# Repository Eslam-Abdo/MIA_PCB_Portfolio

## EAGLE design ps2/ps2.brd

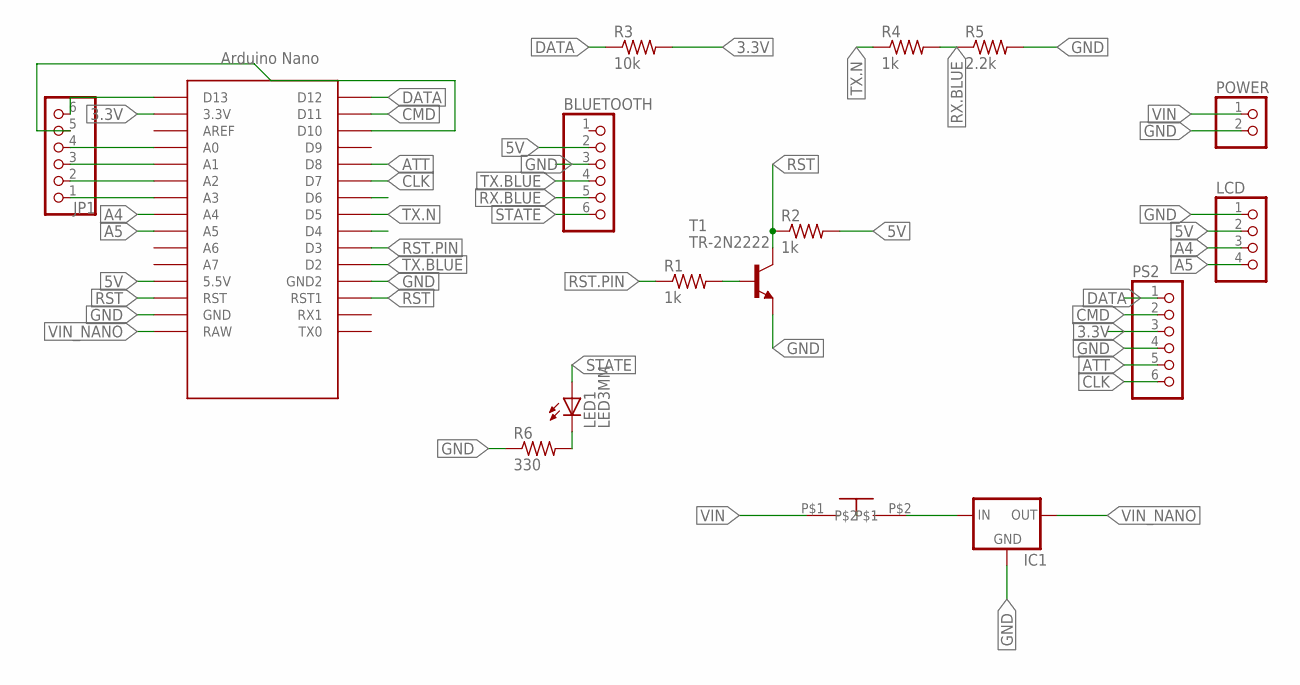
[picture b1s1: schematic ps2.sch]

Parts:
BLUETOOTH: PINHD-1X6; 1X06
IC1: 78XXS
JP1: PINHD-1X6; 1X06
LCD: PINHD-1X4; 1X04
LED1: LED3MM
POWER: PINHD-1X2; 1X02
PS2: PINHD-1X6; 1X06
R1, R2, R4: 1k; 0204/5
R3: 10k; 0204/5
R5: 2.2k; 0204/5
R6: 330; 0204/5
T1: TR-2N2222; TO18
U$1: ARDUINO_NANO; NANO
U$2: SWITCH_2; ON_OFF

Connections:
3.3V: PS2.3, R3.2, U$1.3.3V
5V: BLUETOOTH.2, LCD.2, R2.2, U$1.5V (5.5V)
A4: LCD.3, U$1.A4
A5: LCD.4, U$1.A5
ATT: PS2.5, U$1.D8
CLK: PS2.6, U$1.D7
CMD: PS2.2, U$1.D11
DATA: PS2.1, R3.1, U$1.D12
GND: BLUETOOTH.3, IC1.GND, LCD.1, POWER.2, PS2.4, R5.2, R6.1, T1.1 (E), U$1.GND, U$1.GND1 (GND2)
unnamed: R1.2, T1.2 (B)
unnamed: JP1.1, U$1.A3
unnamed: LED1.K (C), R6.2
unnamed: JP1.2, U$1.A2
unnamed: JP1.3, U$1.A1
unnamed: JP1.4, U$1.A0
unnamed: JP1.6, U$1.D13
unnamed: JP1.5, U$1.D10
unnamed: IC1.IN, U$2.P$2
RST: R2.1, T1.3 (C), U$1.RST, U$1.RST1
RST.PIN: R1.1, U$1.D3
RX.BLUE: BLUETOOTH.5, R4.2, R5.1
STATE: BLUETOOTH.6, LED1.A
TX.BLUE: BLUETOOTH.4, U$1.D2
TX.N: R4.1, U$1.D5
VIN: POWER.1, U$2.P$1
VIN_NANO: IC1.OUT, U$1.RAW

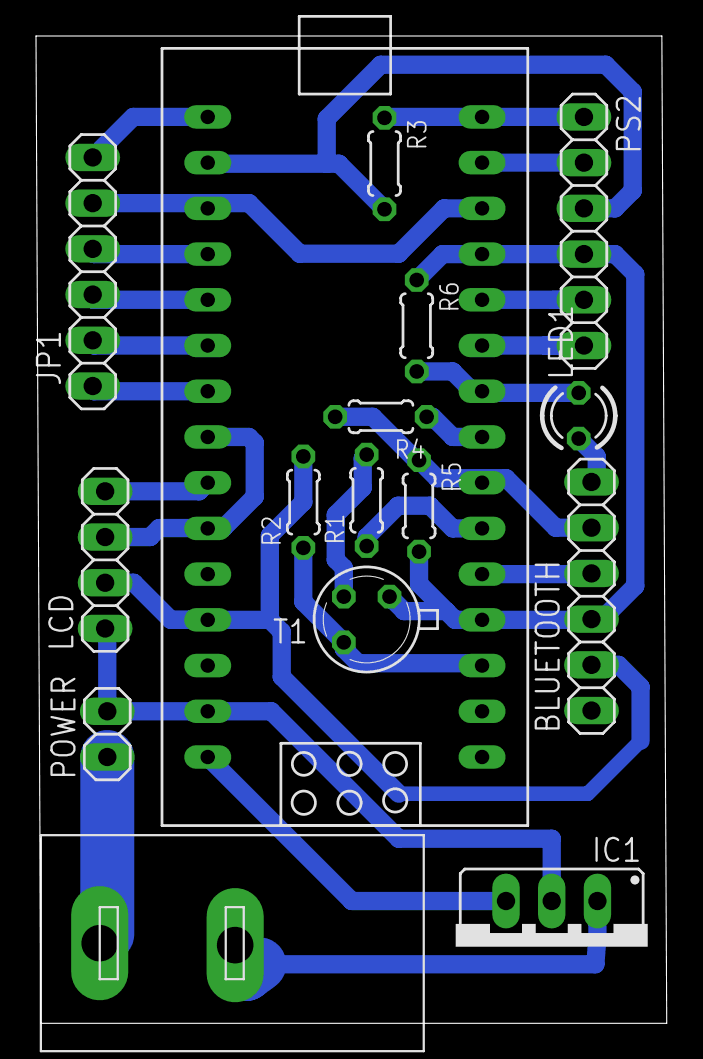
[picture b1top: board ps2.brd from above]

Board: 2 copper layers, 35.0 x 54.9 mm, 16 parts (0 on the bottom side), 26 nets.

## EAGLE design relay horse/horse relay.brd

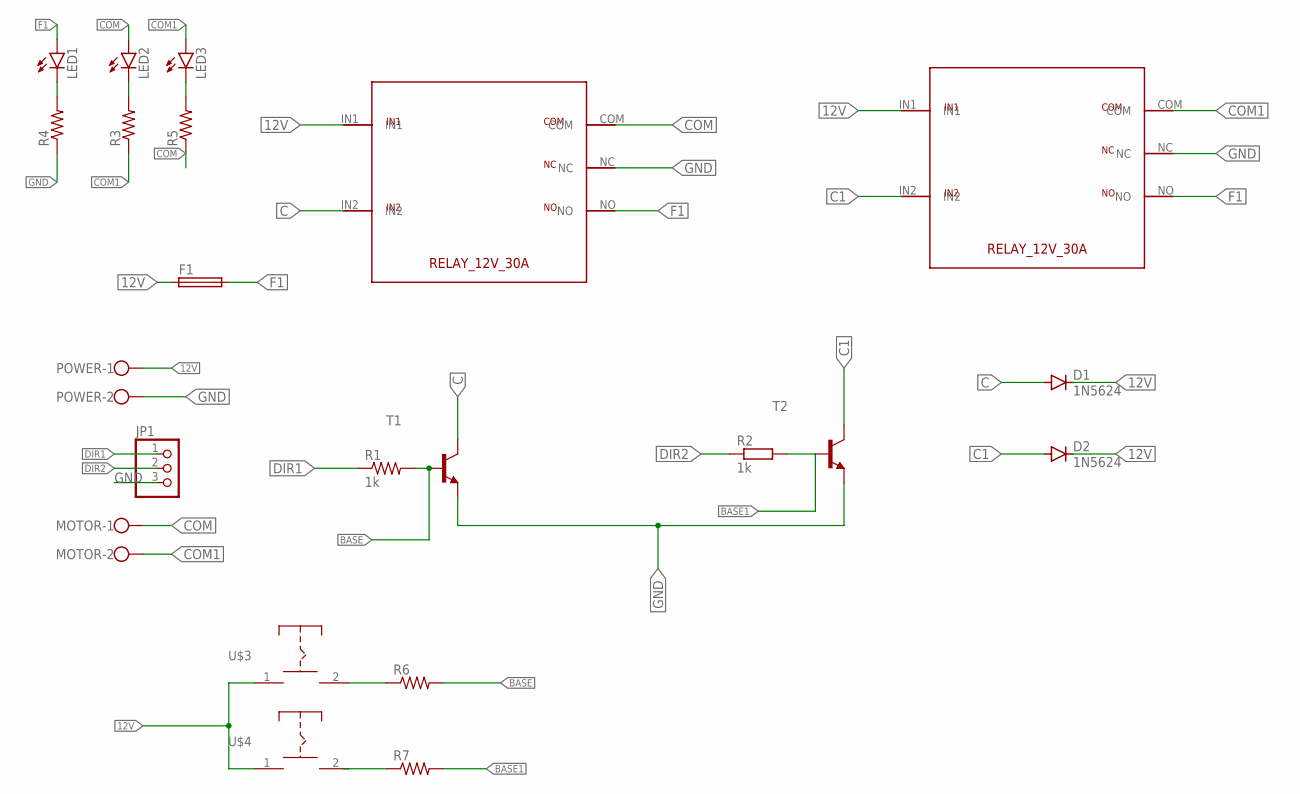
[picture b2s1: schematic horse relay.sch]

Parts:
D1, D2: 1N5624; DO201-15
F1: SH22,5A
JP1: PINHD-1X3; 1X03
LED1: LED5MM
LED2, LED3: LED3MM
MOTOR: W237-113
POWER: W237-113
R1: 1k; 0207/10
R2: 1k; 0204/7
R3, R6: R-US_0207/12; 0207/12
R4, R7: R-US_0204/7; 0204/7
R5: R-US_0207/15; 0207/15
T1, T2: 2N3904-NPN-TO92-EBC; TO92-EBC
U$1, U$2: RELAY_12V_30A
U$3, U$4: PUSHBOTTON

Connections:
12V: D1.C, D2.C, F1.1, POWER.1, U$1.IN1, U$2.IN1, U$3.1, U$4.1
BASE: R1.2, R6.2, T1.B
BASE1: R2.2, R7.2, T2.B
C: D1.A, T1.C, U$1.IN2
C1: D2.A, T2.C, U$2.IN2
COM: LED2.A, MOTOR.1, R5.1, U$1.COM
COM1: LED3.A, MOTOR.2, R3.1, U$2.COM
DIR1: JP1.1, R1.1
DIR2: JP1.2, R2.1
F1: F1.2, LED1.A, U$1.NO, U$2.NO
GND: JP1.3, POWER.2, R4.1, T1.E, T2.E, U$1.NC, U$2.NC
unnamed: LED1.K (C), R4.2
unnamed: LED2.K (C), R3.2
unnamed: LED3.K (C), R5.2
unnamed: R7.1, U$4.2
unnamed: R6.1, U$3.2

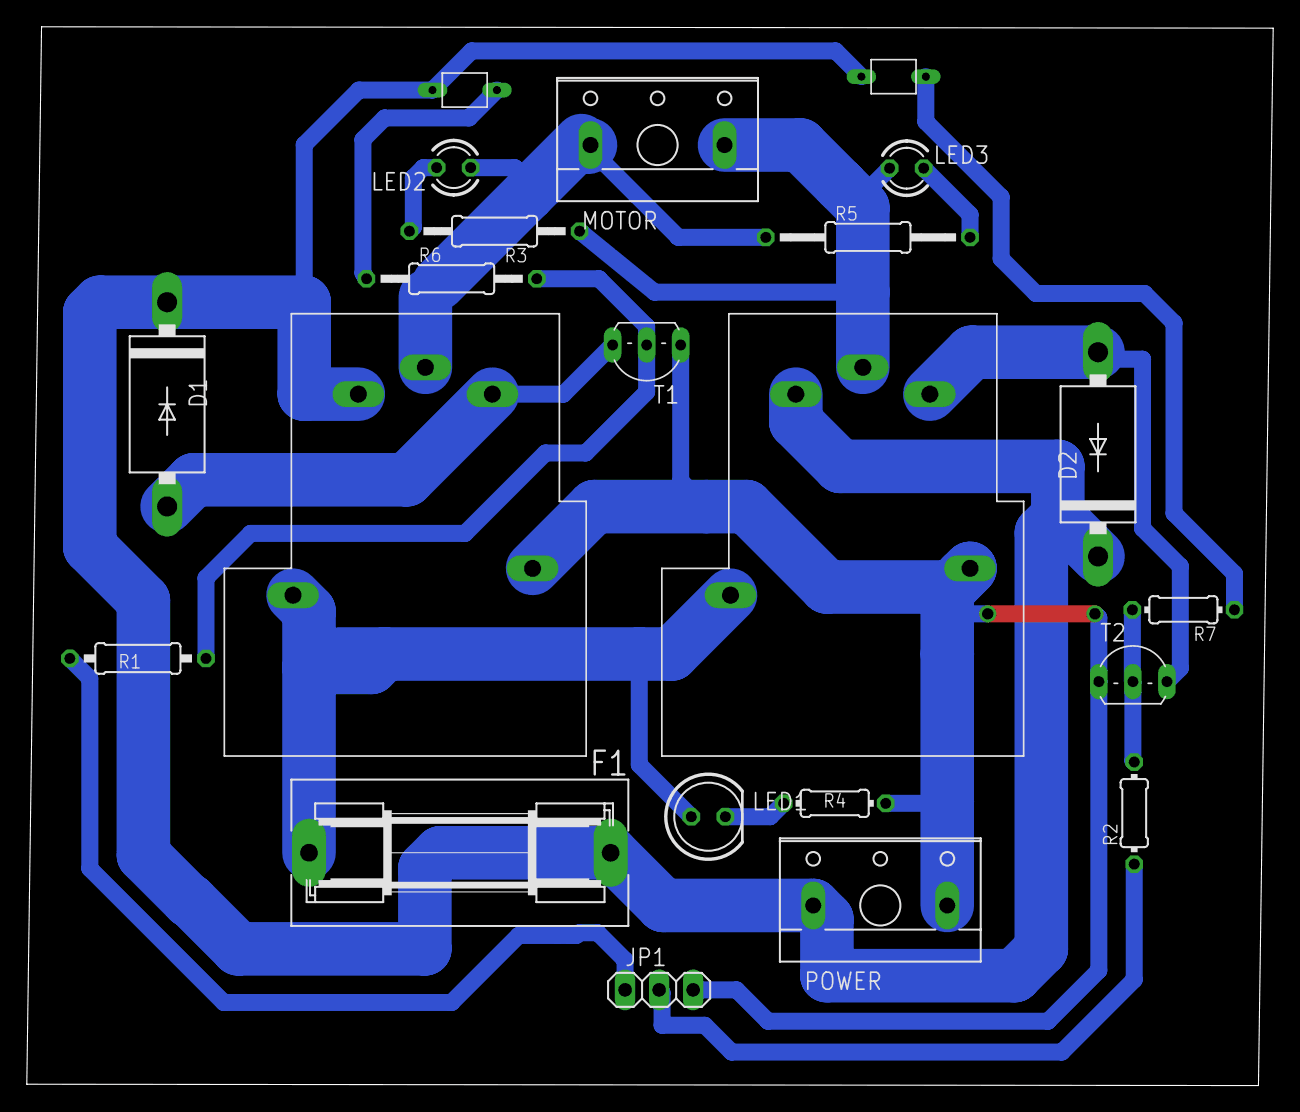
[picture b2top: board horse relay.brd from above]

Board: 2 copper layers, 93.0 x 79.0 mm, 22 parts (0 on the bottom side), 16 nets.

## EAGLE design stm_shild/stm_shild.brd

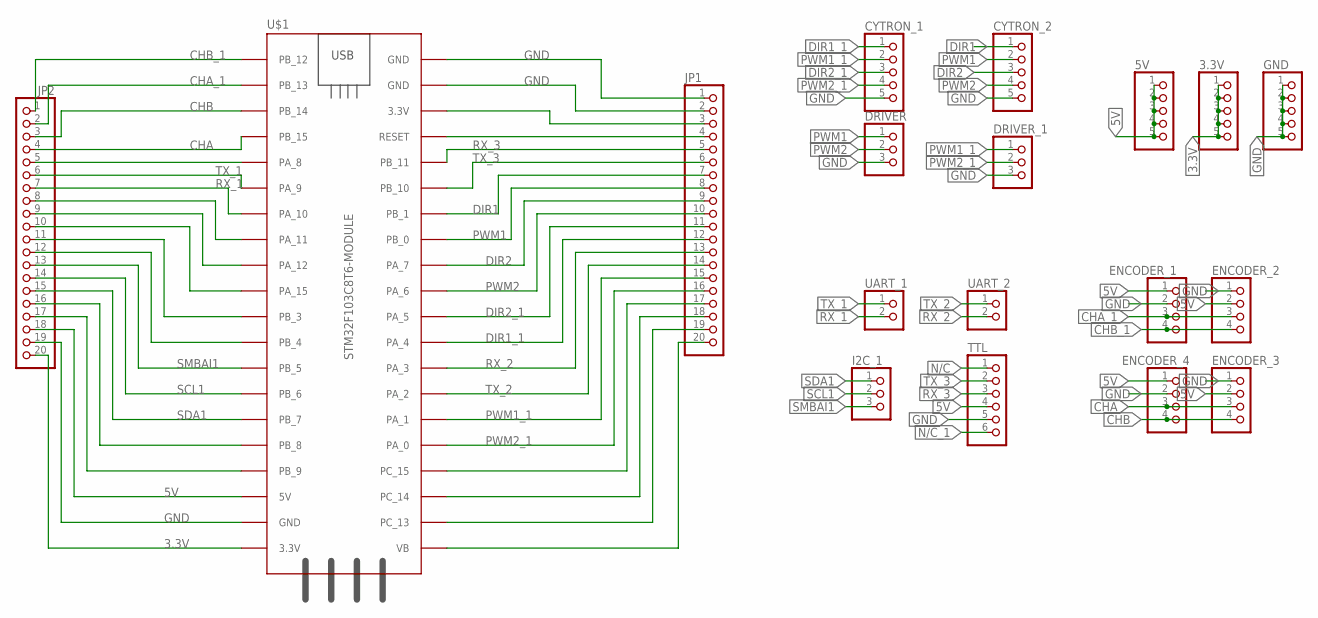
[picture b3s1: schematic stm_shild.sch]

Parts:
3.3V, 5V: PINHD-1X5; 1X05
CYTRON_1, CYTRON_2: PINHD-1X5; 1X05
DRIVER: PINHD-1X3; 1X03
DRIVER_1: PINHD-1X3; 1X03
ENCODER_1, ENCODER_2, ENCODER_3, ENCODER_4: PINHD-1X4; 1X04
GND: PINHD-1X5; 1X05
I2C_1: PINHD-1X3; 1X03
JP1, JP2: PINHD-1X20; 1X20
TTL: PINHD-1X6; 1X06
U$1: STM32F103C8T6-MODULE
UART_1, UART_2: PINHD-1X2; 1X02

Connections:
3.3V: 3.3V.1, 3.3V.2, 3.3V.3, 3.3V.4, 3.3V.5, JP2.20, U$1.3.3V_1 (3.3V)
5V: 5V.1, 5V.2, 5V.3, 5V.4, 5V.5, ENCODER_1.1, ENCODER_2.2, ENCODER_3.2, ENCODER_4.1, JP2.18, TTL.4, U$1.5V
8183: JP2.17, U$1.PB_9
823828: JP2.16, U$1.PB_8
CHA: ENCODER_3.3, ENCODER_4.3, JP2.4, U$1.PB_15
CHA_1: ENCODER_1.3, ENCODER_2.3, JP2.2, U$1.PB_13
CHB: ENCODER_3.4, ENCODER_4.4, JP2.3, U$1.PB_14
CHB_1: ENCODER_1.4, ENCODER_2.4, JP2.1, U$1.PB_12
DIR1: CYTRON_2.1, JP1.7, U$1.PB_1
DIR1_1: CYTRON_1.1, JP1.12, U$1.PA_4
DIR2: CYTRON_2.3, JP1.9, U$1.PA_7
DIR2_1: CYTRON_1.3, JP1.11, U$1.PA_5
GND: CYTRON_1.5, CYTRON_2.5, DRIVER.3, DRIVER_1.3, ENCODER_1.2, ENCODER_2.1, ENCODER_3.1, ENCODER_4.2, GND.1, GND.2, GND.3, GND.4, GND.5, JP1.1, JP1.2, JP2.19, TTL.5, U$1.GND_1 (GND), U$1.GND_2 (GND), U$1.GND_3 (GND)
unnamed: JP1.20, U$1.VB
unnamed: JP1.3, U$1.3.3V_2 (3.3V)
unnamed: JP1.4, U$1.RESET
unnamed: JP1.17, U$1.PC_15
unnamed: JP1.18, U$1.PC_14
unnamed: JP1.19, U$1.PC_13
unnamed: JP2.5, U$1.PA_8
unnamed: JP2.8, U$1.PA_11
unnamed: JP2.9, U$1.PA_12
unnamed: JP2.10, U$1.PA_15
unnamed: JP2.11, U$1.PB_3
unnamed: JP2.12, U$1.PB_4
N/C: TTL.1
N/C_1: TTL.6
PWM1: CYTRON_2.2, DRIVER.1, JP1.8, U$1.PB_0
PWM1_1: CYTRON_1.2, DRIVER_1.1, JP1.15, U$1.PA_1
PWM2: CYTRON_2.4, DRIVER.2, JP1.10, U$1.PA_6
PWM2_1: CYTRON_1.4, DRIVER_1.2, JP1.16, U$1.PA_0
RX_1: JP2.7, U$1.PA_10, UART_1.2
RX_2: JP1.13, U$1.PA_3, UART_2.2
RX_3: JP1.5, TTL.3, U$1.PB_11
SCL1: I2C_1.2, JP2.14, U$1.PB_6
SDA1: I2C_1.1, JP2.15, U$1.PB_7
SMBAI1: I2C_1.3, JP2.13, U$1.PB_5
TX_1: JP2.6, U$1.PA_9, UART_1.1
TX_2: JP1.14, U$1.PA_2, UART_2.1
TX_3: JP1.6, TTL.2, U$1.PB_10

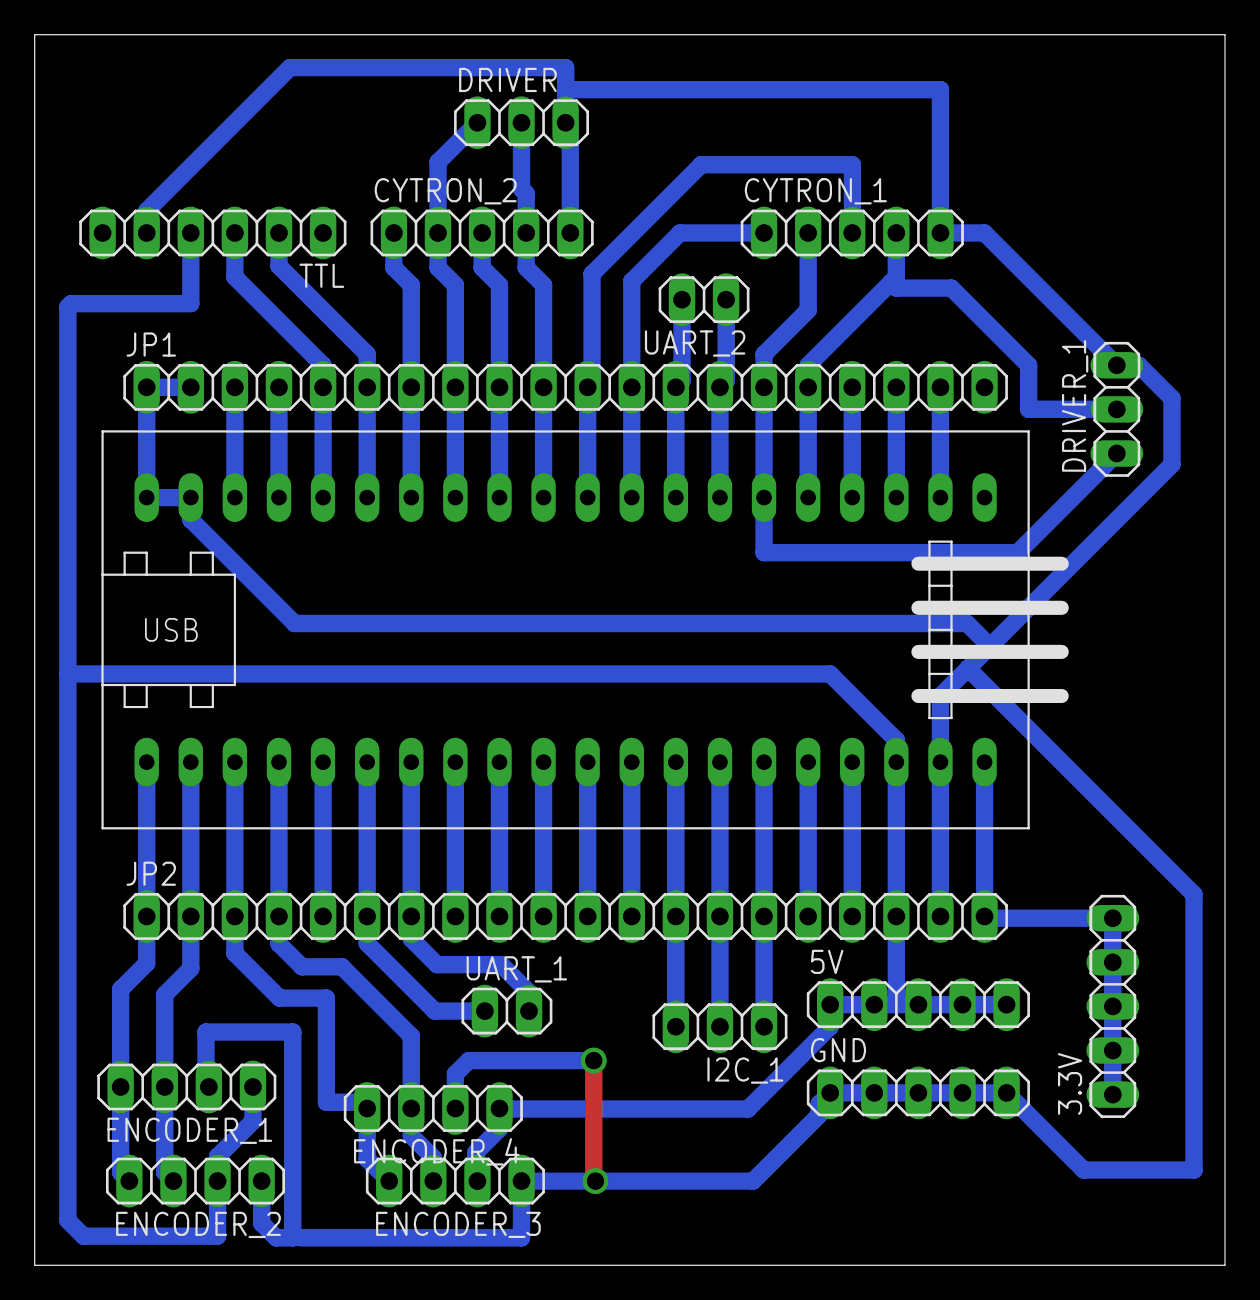
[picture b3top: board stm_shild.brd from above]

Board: 2 copper layers, 68.6 x 70.9 mm, 18 parts (0 on the bottom side), 38 nets.

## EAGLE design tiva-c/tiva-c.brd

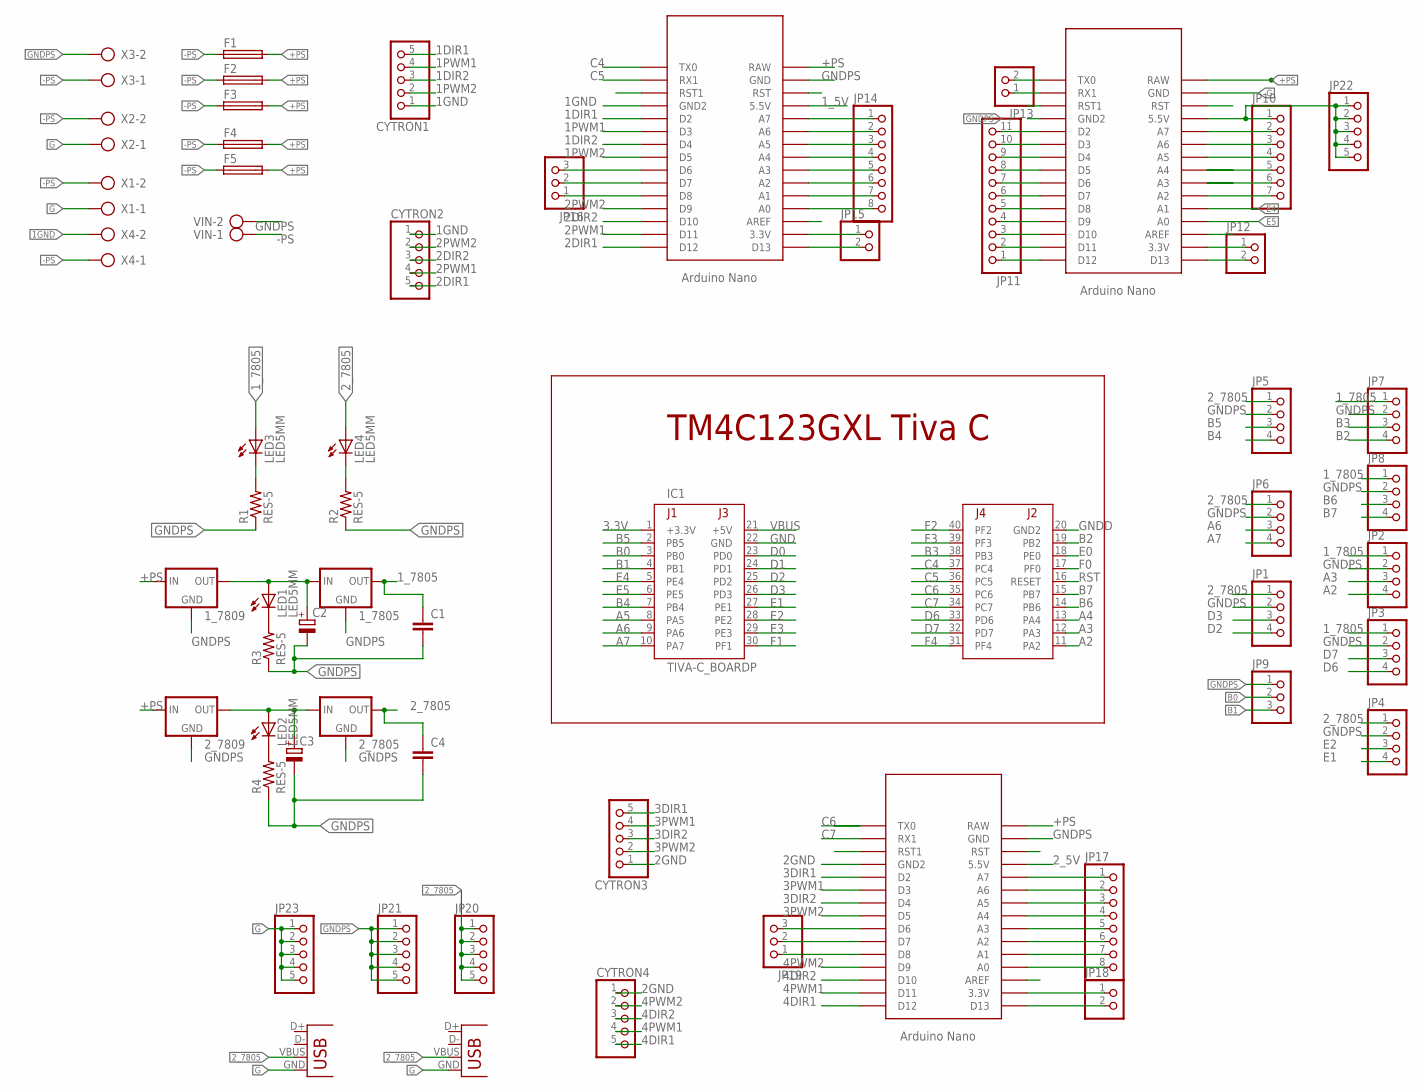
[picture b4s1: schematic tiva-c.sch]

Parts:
1_7805, 1_7809, 2_7805, 2_7809: 78XXS
C1, C4: CAPACITOR; C025-025X050
C2, C3: CAP_POL; E3,5-8
CYTRON1, CYTRON2, CYTRON3, CYTRON4: PINHD-1X5; 1X05
F1, F2, F3, F4, F5: FUSE_HOLDER; SH22,5A
IC1: TIVA-C_BOARDP; TM4C123LAUNCHPAD
JP1, JP2, JP3, JP4, JP5, JP6, JP7, JP8: PINHD-1X4; 1X04
JP9, JP16, JP19: PINHD-1X3; 1X03
JP10: PINHD-1X7; 1X07
JP11: PINHD-1X11; 1X11
JP12, JP13, JP15, JP18: PINHD-1X2; 1X02
JP14, JP17: PINHD-1X8; 1X08
JP20, JP21, JP22, JP23: PINHD-1X5; 1X05
LED1, LED2, LED3, LED4: LED5MM
R1, R2, R3, R4: RES-5; 0204/5
U$1, U$2, U$3: ARDUINO_NANO; NANO
VIN: CON_PTR_2(V_2); AK300/2
X1, X2, X3, X4: CON_PTR_2(V_2); AK300/2
X5, X6: USB-A-H

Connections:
1DIR1: CYTRON1.5, U$3.D2
1DIR2: CYTRON1.3, U$3.D4
1GND: CYTRON1.1, CYTRON2.1, U$3.GND1 (GND2), X4.2
1PWM1: CYTRON1.4, U$3.D3
1PWM2: CYTRON1.2, U$3.D5
1_5V: U$3.5V (5.5V)
1_7805: 1_7805.OUT, C1.1, JP2.1, JP3.1, JP7.1, JP8.1, LED3.A
2DIR1: CYTRON2.5, U$3.D12
2DIR2: CYTRON2.3, U$3.D10
2GND: CYTRON3.1, CYTRON4.1, U$1.GND1 (GND2)
2PWM1: CYTRON2.4, U$3.D11
2PWM2: CYTRON2.2, U$3.D9
2_5V: U$1.5V (5.5V)
2_7805: 2_7805.OUT, C4.1, JP1.1, JP4.1, JP5.1, JP6.1, JP20.1, JP20.2, JP20.3, JP20.4, JP20.5, LED4.A, X5.VBUS, X6.VBUS
3.3V: IC1.1 (+3.3V)
3DIR1: CYTRON3.5, U$1.D2
3DIR2: CYTRON3.3, U$1.D4
3PWM1: CYTRON3.4, U$1.D3
3PWM2: CYTRON3.2, U$1.D5
4DIR1: CYTRON4.5, U$1.D12
4DIR2: CYTRON4.3, U$1.D10
4PWM1: CYTRON4.4, U$1.D11
4PWM2: CYTRON4.2, U$1.D9
+PS: 1_7809.IN, 2_7809.IN, F1.2, F2.2, F3.2, F4.2, F5.2, U$1.RAW, U$2.RAW, U$3.RAW
-PS: F1.1, F2.1, F3.1, F4.1, F5.1, VIN.1, X1.2, X2.2, X3.1, X4.1
A2: IC1.11 (PA2), JP2.4
A3: IC1.12 (PA3), JP2.3
A4: IC1.13 (PA4)
A5: IC1.8 (PA5)
A6: IC1.9 (PA6), JP6.3
A7: IC1.10 (PA7), JP6.4
B0: IC1.3 (PB0), JP9.2
B1: IC1.4 (PB1), JP9.3
B2: IC1.19 (PB2), JP7.4
B3: IC1.38 (PB3), JP7.3
B4: IC1.7 (PB4), JP5.4
B5: IC1.2 (PB5), JP5.3
B6: IC1.14 (PB6), JP8.3
B7: IC1.15 (PB7), JP8.4
C4: IC1.37 (PC4), U$3.TX0
C5: IC1.36 (PC5), U$3.RX1
C6: IC1.35 (PC6), U$1.TX0
C7: IC1.34 (PC7), U$1.RX1
D0: IC1.23 (PD0)
D1: IC1.24 (PD1)
D2: IC1.25 (PD2), JP1.4
D3: IC1.26 (PD3), JP1.3
D6: IC1.33 (PD6), JP3.4
D7: IC1.32 (PD7), JP3.3
E0: IC1.18 (PE0)
E1: IC1.27 (PE1), JP4.4
E2: IC1.28 (PE2), JP4.3
E3: IC1.29 (PE3)
E4: IC1.5 (PE4), U$2.A1
E5: IC1.6 (PE5), U$2.A0
F0: IC1.17 (PF0)
F1: IC1.30 (PF1)
F2: IC1.40 (PF2)
F3: IC1.39 (PF3)
F4: IC1.31 (PF4)
G: JP23.1, JP23.2, JP23.3, JP23.4, JP23.5, U$2.GND, X1.1, X2.1, X5.GND, X6.GND
GND: IC1.22 (GND)
GNDD: IC1.20 (GND2)
GNDPS: 1_7805.GND, 1_7809.GND, 2_7805.GND, 2_7809.GND, C1.2, C2.-, C3.-, C4.2, JP1.2, JP2.2, JP3.2, JP4.2, JP5.2, JP6.2, JP7.2, JP8.2, JP9.1, JP21.1, JP21.2, JP21.3, JP21.4, JP21.5, R1.1, R2.1, R3.1, R4.1, U$1.GND, U$2.GND1 (GND2), U$3.GND, VIN.2, X3.2
unnamed: 2_7805.IN, 2_7809.OUT, C3.+, LED2.A
unnamed: 1_7805.IN, 1_7809.OUT, C2.+, LED1.A
unnamed: LED3.K (C), R1.2
unnamed: LED4.K (C), R2.2
unnamed: LED1.K (C), R3.2
unnamed: LED2.K (C), R4.2
unnamed: JP12.1, U$2.3.3V
unnamed: JP10.2, U$2.A7
unnamed: JP10.3, U$2.A6
unnamed: JP10.4, U$2.A5
unnamed: JP10.5, U$2.A4
unnamed: JP10.6, U$2.A3
unnamed: JP10.7, U$2.A2
unnamed: JP11.1, U$2.D12
unnamed: JP11.2, U$2.D11
unnamed: JP11.3, U$2.D10
unnamed: JP11.4, U$2.D9
unnamed: JP11.5, U$2.D8
unnamed: JP11.6, U$2.D7
unnamed: JP11.7, U$2.D6
unnamed: JP11.8, U$2.D5
unnamed: JP11.9, U$2.D4
unnamed: JP11.10, U$2.D3
unnamed: JP11.11, U$2.D2
unnamed: JP12.2, U$2.D13
unnamed: JP13.1, U$2.RX1
unnamed: JP13.2, U$2.TX0
unnamed: JP14.1, U$3.A7
unnamed: JP14.2, U$3.A6
unnamed: JP14.3, U$3.A5
unnamed: JP14.4, U$3.A4
unnamed: JP14.5, U$3.A3
unnamed: JP14.6, U$3.A2
unnamed: JP14.7, U$3.A1
unnamed: JP14.8, U$3.A0
unnamed: JP15.1, U$3.3.3V
unnamed: JP15.2, U$3.D13
unnamed: JP16.1, U$3.D8
unnamed: JP16.2, U$3.D7
unnamed: JP16.3, U$3.D6
unnamed: JP17.1, U$1.A7
unnamed: JP17.2, U$1.A6
unnamed: JP17.3, U$1.A5
unnamed: JP17.4, U$1.A4
unnamed: JP17.5, U$1.A3
unnamed: JP17.6, U$1.A2
unnamed: JP17.7, U$1.A1
unnamed: JP17.8, U$1.A0
unnamed: JP18.1, U$1.3.3V
unnamed: JP18.2, U$1.D13
unnamed: JP19.1, U$1.D8
unnamed: JP19.2, U$1.D7
unnamed: JP19.3, U$1.D6
unnamed: JP10.1, JP22.1, JP22.2, JP22.3, JP22.4, JP22.5, U$2.5V (5.5V)
RST: IC1.16 (RESET)
VBUS: IC1.21 (+5V)

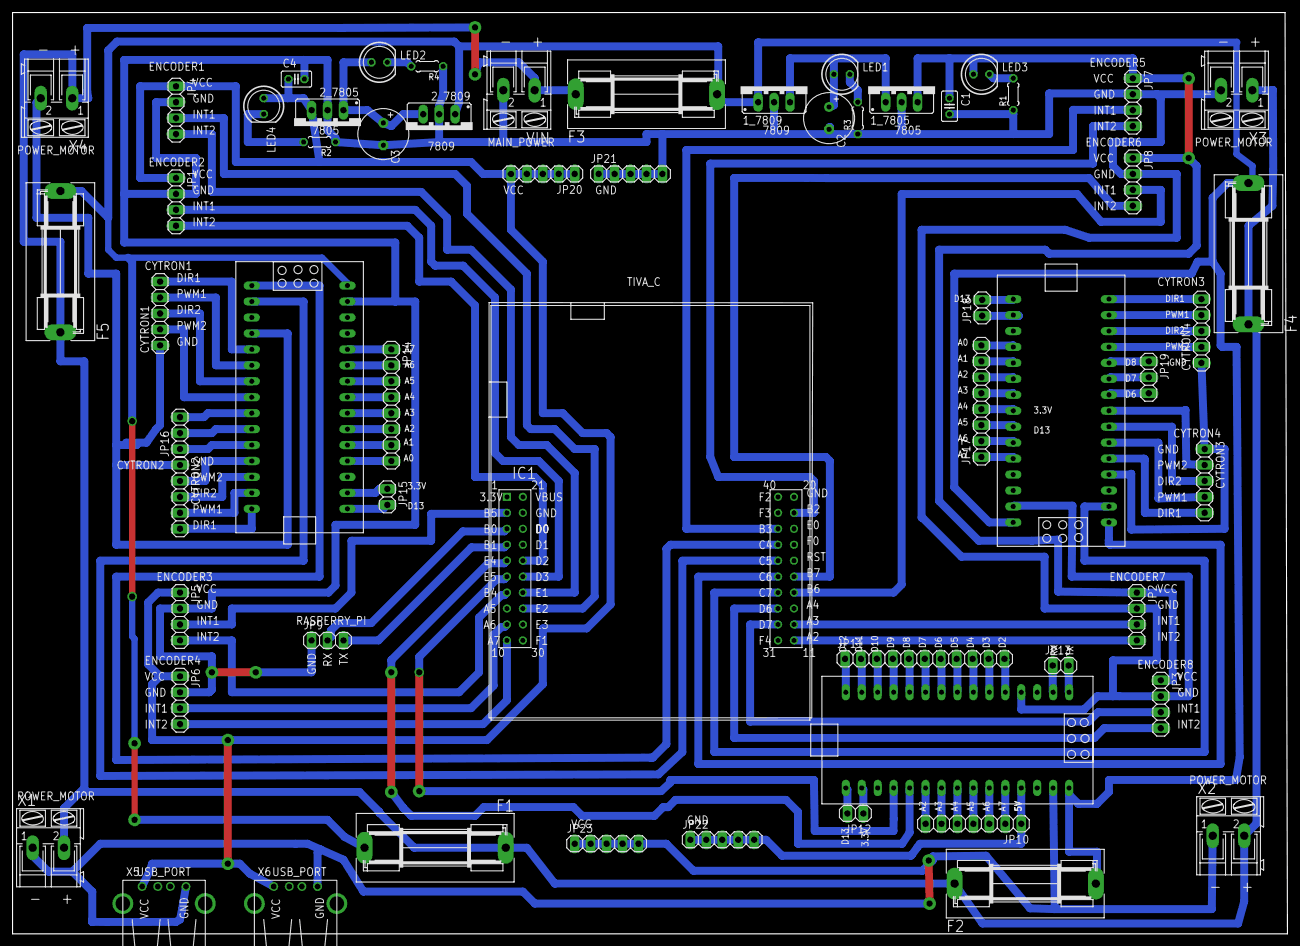
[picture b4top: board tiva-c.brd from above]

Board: 2 copper layers, 203.1 x 146.7 mm, 59 parts (0 on the bottom side), 102 nets.

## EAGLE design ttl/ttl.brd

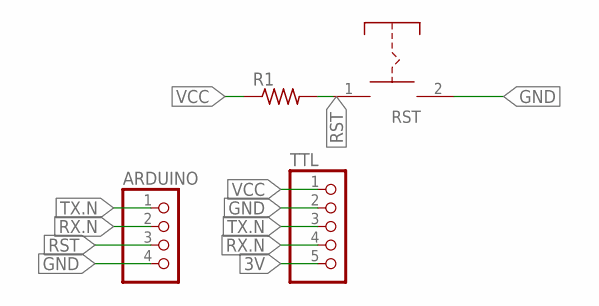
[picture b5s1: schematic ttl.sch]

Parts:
ARDUINO: PINHD-1X4; 1X04
R1: R-US_0204/5; 0204/5
RST: PUSHBOTTON
TTL: PINHD-1X5; 1X05

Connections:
3V: TTL.5
GND: ARDUINO.4, RST.2, TTL.2
RST: ARDUINO.3, R1.2, RST.1
RX.N: ARDUINO.2, TTL.4
TX.N: ARDUINO.1, TTL.3
VCC: R1.1, TTL.1

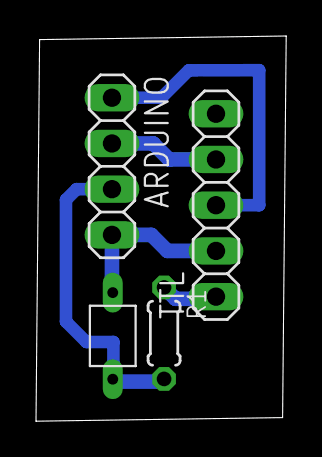
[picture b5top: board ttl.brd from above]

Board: 2 copper layers, 13.9 x 21.4 mm, 4 parts (0 on the bottom side), 5 nets.
